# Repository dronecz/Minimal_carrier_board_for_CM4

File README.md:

# Minimal carrier board for Compute Module 4

This board is based on design from [Prof. Fartsparkle´s](https://hackaday.io/project/175832-minimal-raspberry-pi-cm-4-carrier). I made it 2 layer board and changed slot for SD card. 

If you are interested, I have some boards for you at my [Tindie](https://www.tindie.com/products/dronecz/minimal-carrier-board-for-compute-module-4/) store. 

You can also find STEP files for revision A and D in _STEP files_ directory. 

##### A designed following revisions:

- **rev.A**

This is just copy of the design from Timon. I just added 2x7 pin header and made shape of the board to the size of the Einsy board so I can use it for Octoprint. 

Board is tested and working. There is UART connection at that 2x7 pin header connected to the GPIO´s at CM4. There is slight problem with cables for HDMI and USB, but it can be solved with right cables.  

**WARNING** : The pinout for Einsy board is mirrored so I do not take any responsibility for damage which can be cause by this. You can change that in files and made your own board.

- **rev.B** 

I redesigned whole board and made it little bit bigger. Added 3.2mm mounting holes to each corner, added boot button for versions of CM4 with eMMC onboard (working), added connector for camera and added standard 40-pin header for Raspberry Pi.

I did not made this board yet but I did test distances between cables and rearanged them so they should not colide. Height of camera connector should be OK beneeth CM4, but this need to be tested. 

- **rev.B_alt**

This is same board as rev.B, but there are 22-pin connectors which are same as those used at official IO board. 

This version of the board was not manufactured and probably will never be. 

- **rev.C**

Layout of the board is same with **rev.B** but I did move CM4 about 2 mm up and camera connector about 1 mm down. Half of the board was routed again .**This revision was not manufactured and it is not tested!** 

- **rev.D**

This version of the board is working, except camera connector because I did not routed camera connections as differential pairs. I made and sold about 30 boards without any complains, so the design is validated. 

- **rev.E**

This is same board as rev.D, but with differential pairs fix for camera connector. **This revision was not yet manufactured so I can not garantee that the connector for camera will work.**

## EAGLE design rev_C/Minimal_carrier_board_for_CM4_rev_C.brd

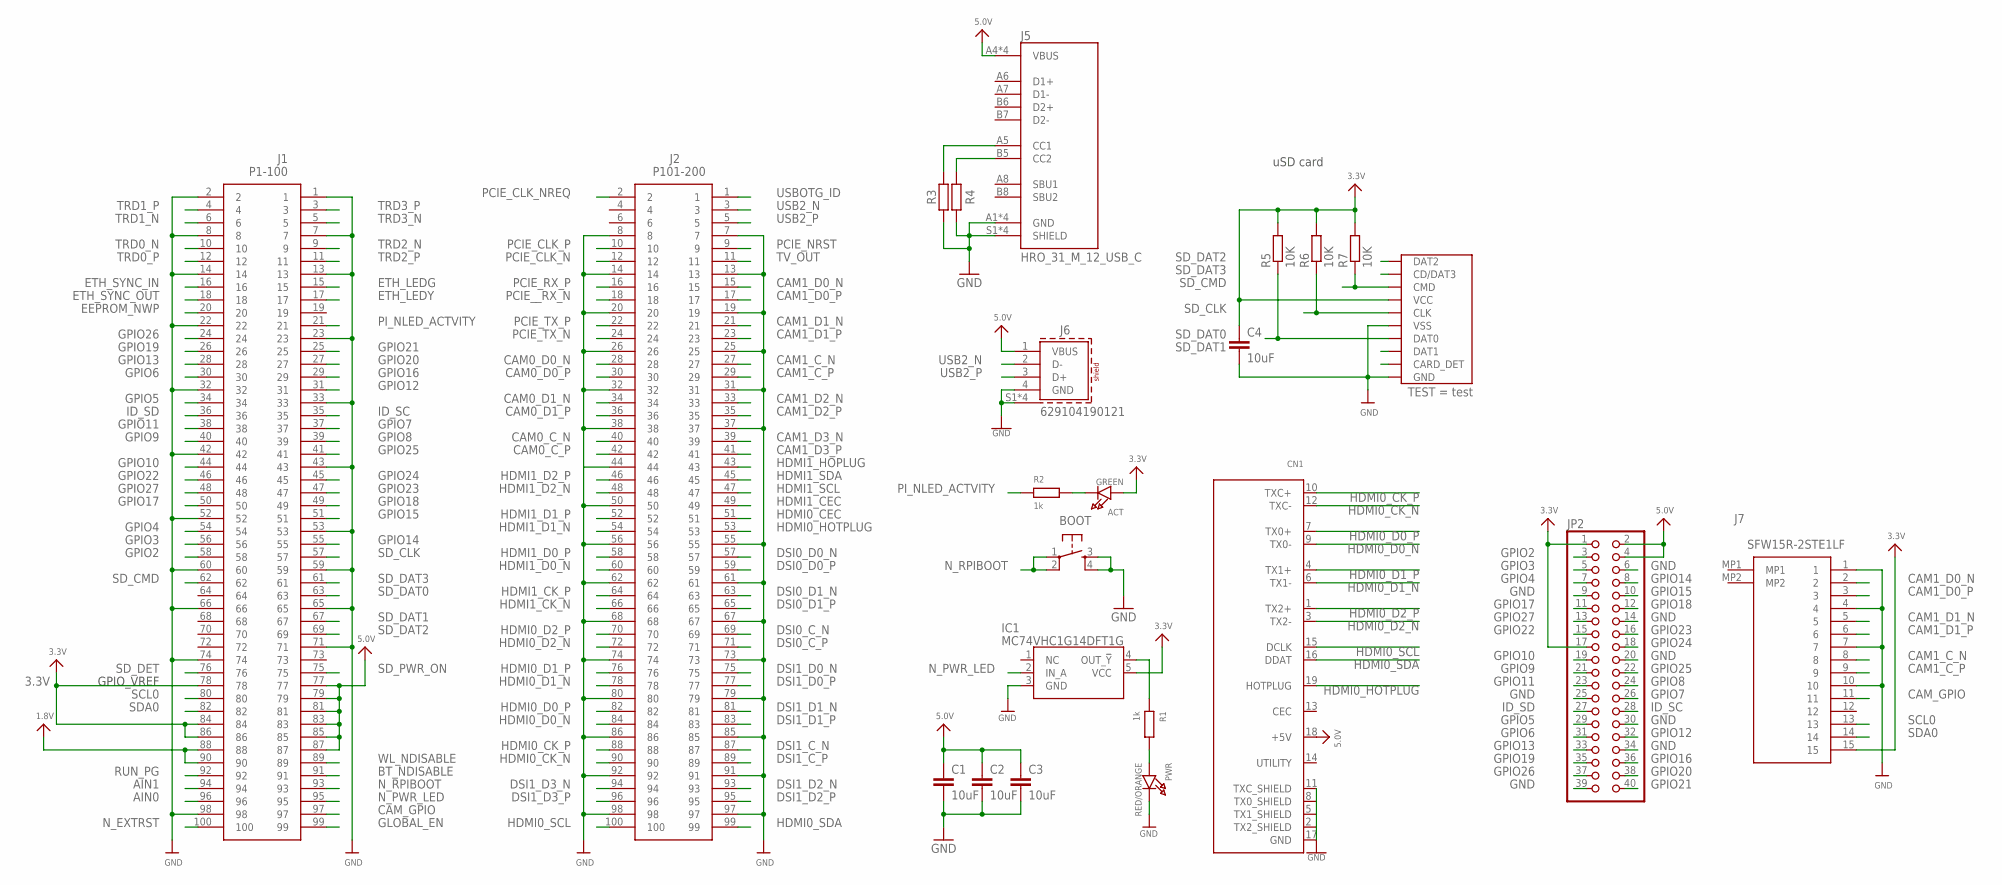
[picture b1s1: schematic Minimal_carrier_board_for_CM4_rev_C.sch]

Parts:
ACT: GREEN; CHIPLED_0805_NOOUTLINE
BOOT: TACTILE_SWITCHE_5X5_MICRO_; TACTILE_SWITCH_5X5_MICRO
C1, C2, C3, C4: 10uF; C0805
CN1: HDMI_MOLEX_47151-0001
IC1: MC74VHC1G14DFT1G; SOT65P210X110-5N
J1: P1-100; DF40C100DS04V51
J2: P101-200; DF40C100DS04V51
J5: HRO_31_M_12_USB_C
J6: 629104190121
J7: SFW15R-2STE1LF; SFW15R2STE1LF
JP2: PINHD-2X20; 2X20
PWR: RED/ORANGE; CHIPLED_0805_NOOUTLINE
R1, R2: 1k; R0805
R3, R4: 5.1k; R0805
R5, R6, R7: 10K; R0805
SD_CARD: MICRO_SD_CARD_; TFP09-2--12B

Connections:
1.8V: J1.88, J1.90
3.3V: ACT.A, C4.1, IC1.5 (VCC), J1.78, J1.84, J1.86, J7.15, JP2.1, JP2.17, R5.2, R6.2, R7.2, SD_CARD.VCC
5.0V: C1.1, C2.1, C3.1, CN1.18 (+5V), J1.77, J1.79, J1.81, J1.83, J1.85, J1.87, J5.A4 (VBUS), J5.A9 (VBUS), J5.B4 (VBUS), J5.B9 (VBUS), J6.1 (VBUS), JP2.2, JP2.4
AIN0: J1.96
AIN1: J1.94
BT_NDISABLE: J1.91
CAM0_C_N: J2.40
CAM0_C_P: J2.42
CAM0_D0_N: J2.28
CAM0_D0_P: J2.30
CAM0_D1_N: J2.34
CAM0_D1_P: J2.36
CAM1_C_N: J2.27, J7.8
CAM1_C_P: J2.29, J7.9
CAM1_D0_N: J2.15, J7.2
CAM1_D0_P: J2.17, J7.3
CAM1_D1_N: J2.21, J7.5
CAM1_D1_P: J2.23, J7.6
CAM1_D2_N: J2.33
CAM1_D2_P: J2.35
CAM1_D3_N: J2.39
CAM1_D3_P: J2.41
CAM_GPIO: J1.97, J7.11
DSI0_C_N: J2.69
DSI0_C_P: J2.71
DSI0_D0_N: J2.57
DSI0_D0_P: J2.59
DSI0_D1_N: J2.63
DSI0_D1_P: J2.65
DSI1_C_N: J2.87
DSI1_C_P: J2.89
DSI1_D0_N: J2.75
DSI1_D0_P: J2.77
DSI1_D1_N: J2.81
DSI1_D1_P: J2.83
DSI1_D2_N: J2.93
DSI1_D2_P: J2.95
DSI1_D3_N: J2.94
DSI1_D3_P: J2.96
EEPROM_NWP: J1.20
ETH_LEDG: J1.15
ETH_LEDY: J1.17
ETH_SYNC_IN: J1.16
ETH_SYNC_OUT: J1.18
GLOBAL_EN: J1.99
GND: BOOT.3, BOOT.4, C1.2, C2.2, C3.2, C4.2, CN1.2 (TX2_SHIELD), CN1.5 (TX1_SHIELD), CN1.8 (TX0_SHIELD), CN1.11 (TXC_SHIELD), CN1.17 (GND), CN1.P$1 (GND), CN1.P$2 (GND), CN1.P$3 (GND), CN1.P$4 (GND), IC1.3 (GND), J1.1, J1.2, J1.7, J1.8, J1.13, J1.14, J1.22, J1.23, J1.32, J1.33, J1.42, J1.43, J1.52, J1.53, J1.59, J1.60, J1.65, J1.66, J1.71, J1.74, J1.98, J2.7, J2.8, J2.13, J2.14, J2.19, J2.20, J2.25, J2.26, J2.31, J2.32, J2.37, J2.38, J2.44, J2.50, J2.55, J2.56, J2.61, J2.62, J2.67, J2.68, J2.73, J2.74, J2.79, J2.80, J2.85, J2.86, J2.91, J2.92, J2.97, J2.98, J5.A1 (GND), J5.A12 (GND), J5.B1 (GND), J5.B12 (GND), J5.S1 (SHIELD), J5.S2 (SHIELD), J5.S3 (SHIELD), J5.S4 (SHIELD), J6.4 (GND), J6.S1 (SHIELD), J6.S2 (SHIELD), J6.S3 (SHIELD), J6.S4 (SHIELD), J7.1, J7.4, J7.7, J7.10, JP2.6, JP2.9, JP2.14, JP2.20, JP2.25, JP2.30, JP2.34, JP2.39, PWR.C, R3.1, R4.2, SD_CARD.GND, SD_CARD.GND@1 (GND), SD_CARD.GND@2 (GND), SD_CARD.GND@3 (VSS), SD_CARD.VSS (GND)
GPIO2: J1.58, JP2.3
GPIO3: J1.56, JP2.5
GPIO4: J1.54, JP2.7
GPIO5: J1.34, JP2.29
GPIO6: J1.30, JP2.31
GPIO7: J1.37, JP2.26
GPIO8: J1.39, JP2.24
GPIO9: J1.40, JP2.21
GPIO10: J1.44, JP2.19
GPIO11: J1.38, JP2.23
GPIO12: J1.31, JP2.32
GPIO13: J1.28, JP2.33
GPIO14: J1.55, JP2.8
GPIO15: J1.51, JP2.10
GPIO16: J1.29, JP2.36
GPIO17: J1.50, JP2.11
GPIO18: J1.49, JP2.12
GPIO19: J1.26, JP2.35
GPIO20: J1.27, JP2.38
GPIO21: J1.25, JP2.40
GPIO22: J1.46, JP2.15
GPIO23: J1.47, JP2.16
GPIO24: J1.45, JP2.18
GPIO25: J1.41, JP2.22
GPIO26: J1.24, JP2.37
GPIO27: J1.48, JP2.13
HDMI0_CEC: J2.51
HDMI0_CK_N: CN1.12 (TXC-), J2.90
HDMI0_CK_P: CN1.10 (TXC+), J2.88
HDMI0_D0_N: CN1.9 (TX0-), J2.84
HDMI0_D0_P: CN1.7 (TX0+), J2.82
HDMI0_D1_N: CN1.6 (TX1-), J2.78
HDMI0_D1_P: CN1.4 (TX1+), J2.76
HDMI0_D2_N: CN1.3 (TX2-), J2.72
HDMI0_D2_P: CN1.1 (TX2+), J2.70
HDMI0_HOTPLUG: CN1.19 (HOTPLUG), J2.53
HDMI0_SCL: CN1.15 (DCLK), J2.100
HDMI0_SDA: CN1.16 (DDAT), J2.99
HDMI1_CEC: J2.49
HDMI1_CK_N: J2.66
HDMI1_CK_P: J2.64
HDMI1_D0_N: J2.60
HDMI1_D0_P: J2.58
HDMI1_D1_N: J2.54
HDMI1_D1_P: J2.52
HDMI1_D2_N: J2.48
HDMI1_D2_P: J2.46
HDMI1_HOPLUG: J2.43
HDMI1_SCL: J2.47
HDMI1_SDA: J2.45
ID_SC: J1.35, JP2.28
ID_SD: J1.36, JP2.27
unnamed: ACT.C, R2.2
unnamed: J5.B5 (CC2), R4.1
unnamed: IC1.4 (OUT_!Y), R1.1
unnamed: J5.A5 (CC1), R3.2
unnamed: PWR.A, R1.2
N_EXTRST: J1.100
N_PWR_LED: IC1.2 (IN_A), J1.95
N_RPIBOOT: BOOT.1, BOOT.2, J1.93
PCIE_CLK_N: J2.12
PCIE_CLK_NREQ: J2.2
PCIE_CLK_P: J2.10
PCIE_NRST: J2.9
PCIE_RX_P: J2.16
PCIE_TX_N: J2.24
PCIE_TX_P: J2.22
PCIE__RX_N: J2.18
PI_NLED_ACTVITY: J1.21, R2.1
RUN_PG: J1.92
SCL0: J1.80, J7.13
SDA0: J1.82, J7.14
SD_CLK: J1.57, R6.1, SD_CARD.CLK
SD_CMD: J1.62, R7.1, SD_CARD.CMD
SD_DAT0: J1.63, R5.1, SD_CARD.DAT0
SD_DAT1: J1.67, SD_CARD.DAT1
SD_DAT2: J1.69, SD_CARD.DAT2
SD_DAT3: J1.61, SD_CARD.CD/DAT3
SD_DET: J1.76
SD_PWR_ON: J1.75
TRD0_N: J1.10
TRD0_P: J1.12
TRD1_N: J1.6
TRD1_P: J1.4
TRD2_N: J1.9
TRD2_P: J1.11
TRD3_N: J1.5
TRD3_P: J1.3
TV_OUT: J2.11
USB2_N: J2.3, J6.2 (D-)
USB2_P: J2.5, J6.3 (D+)
USBOTG_ID: J2.1
WL_NDISABLE: J1.89

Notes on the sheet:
uSD card
GPIO_VREF

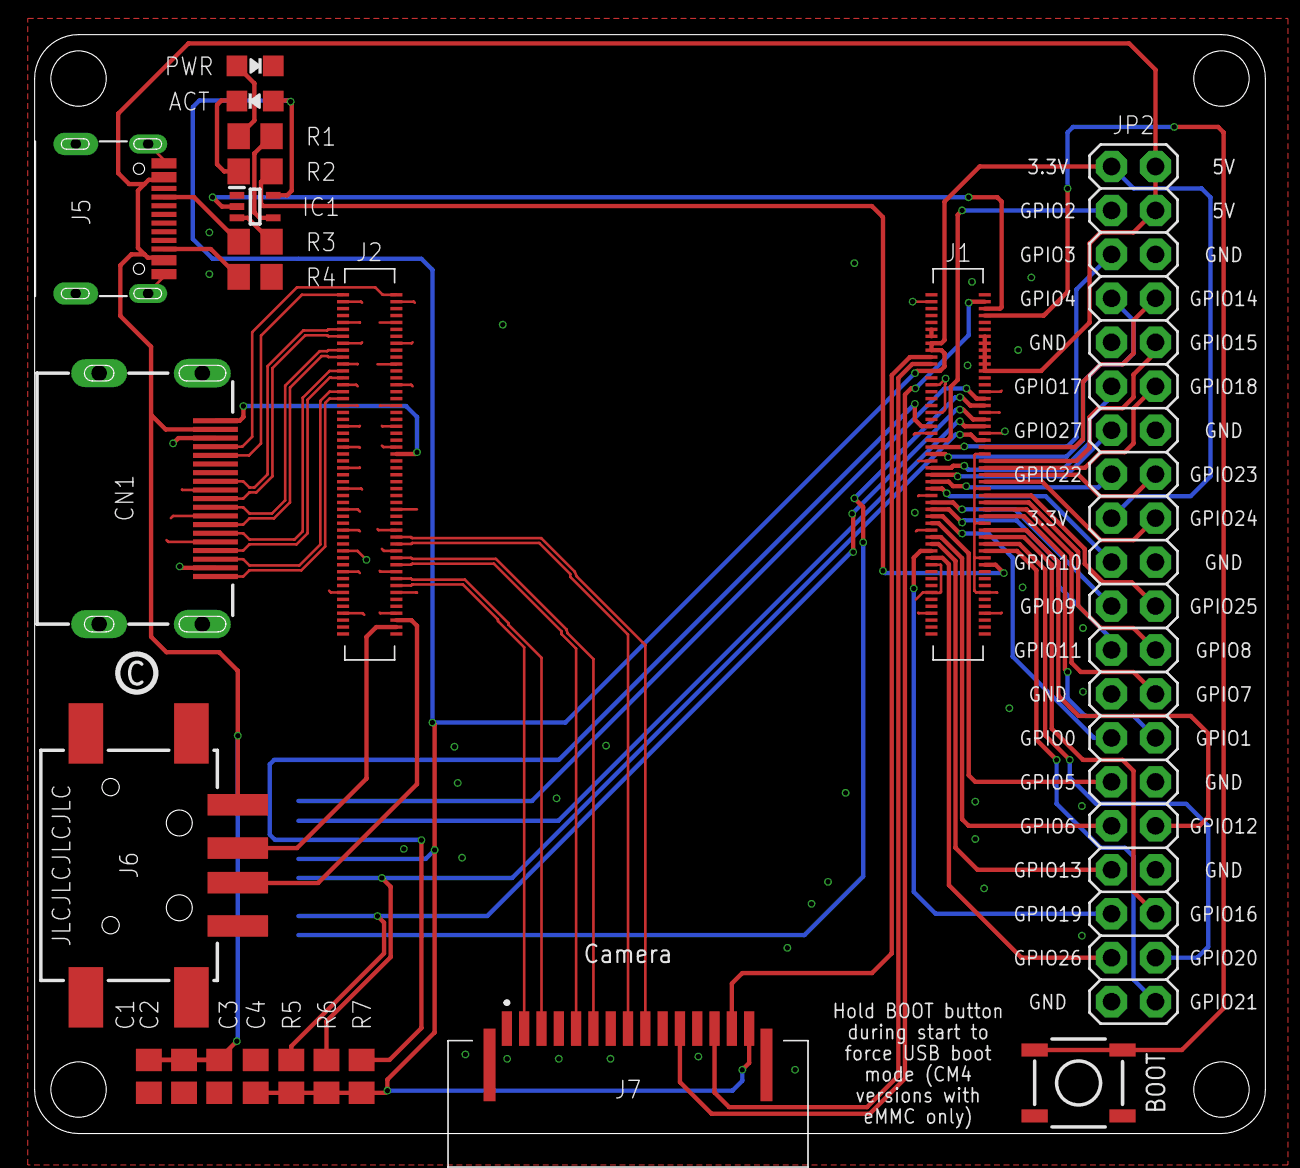
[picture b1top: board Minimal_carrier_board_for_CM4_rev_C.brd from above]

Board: 2 copper layers, 71.1 x 63.5 mm, 23 parts (1 on the bottom side), 68 nets.

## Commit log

2021-01-06 Initial commit
    - pictures and files for Autodesk Eagle
2021-01-06 Typo fix
2021-01-11 Added connector for camera and DSI display
2021-01-12 Update
    - moved USB-C, HDMI and USB-A connector to ensure that cables will not colide
    - changed USB-C and HDMI connector to my library so I can display width od the connectors
    - updated README accordingly
2021-01-13 Update
    - renamed files so there are now 2 versions of rev.B:
    rev.B now have 15-pin connector for RPi camera module
    rev.B_alt have 22-pin connector for RPi camera module and DSI display
    - added/updated pictures for both versions of the board
    - updated README accordingly
2021-01-15 Update README.md
    - added link to product at Tindie
2021-02-04 Aded pictures from CAD fro rev.B
2021-02-04 Change of address for picture in main page
2021-02-05 Update
    - updated README
    - upload rev.C files
    - upload rev.C images
2021-02-05 Changed names of the pictures
2023-02-06 Update
    - updated README.md
    - added rev.D and rev.E files (check README)

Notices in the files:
parts and their libraries:
microbuilder: This work is placed in the public domain, and may be freely used for commercial and non-commercial work with the following conditions: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
SparkFun-PowerSymbols: Licensing: Creative Commons ShareAlike 4.0 International - https://creativecommons.org/licenses/by-sa/4.0
